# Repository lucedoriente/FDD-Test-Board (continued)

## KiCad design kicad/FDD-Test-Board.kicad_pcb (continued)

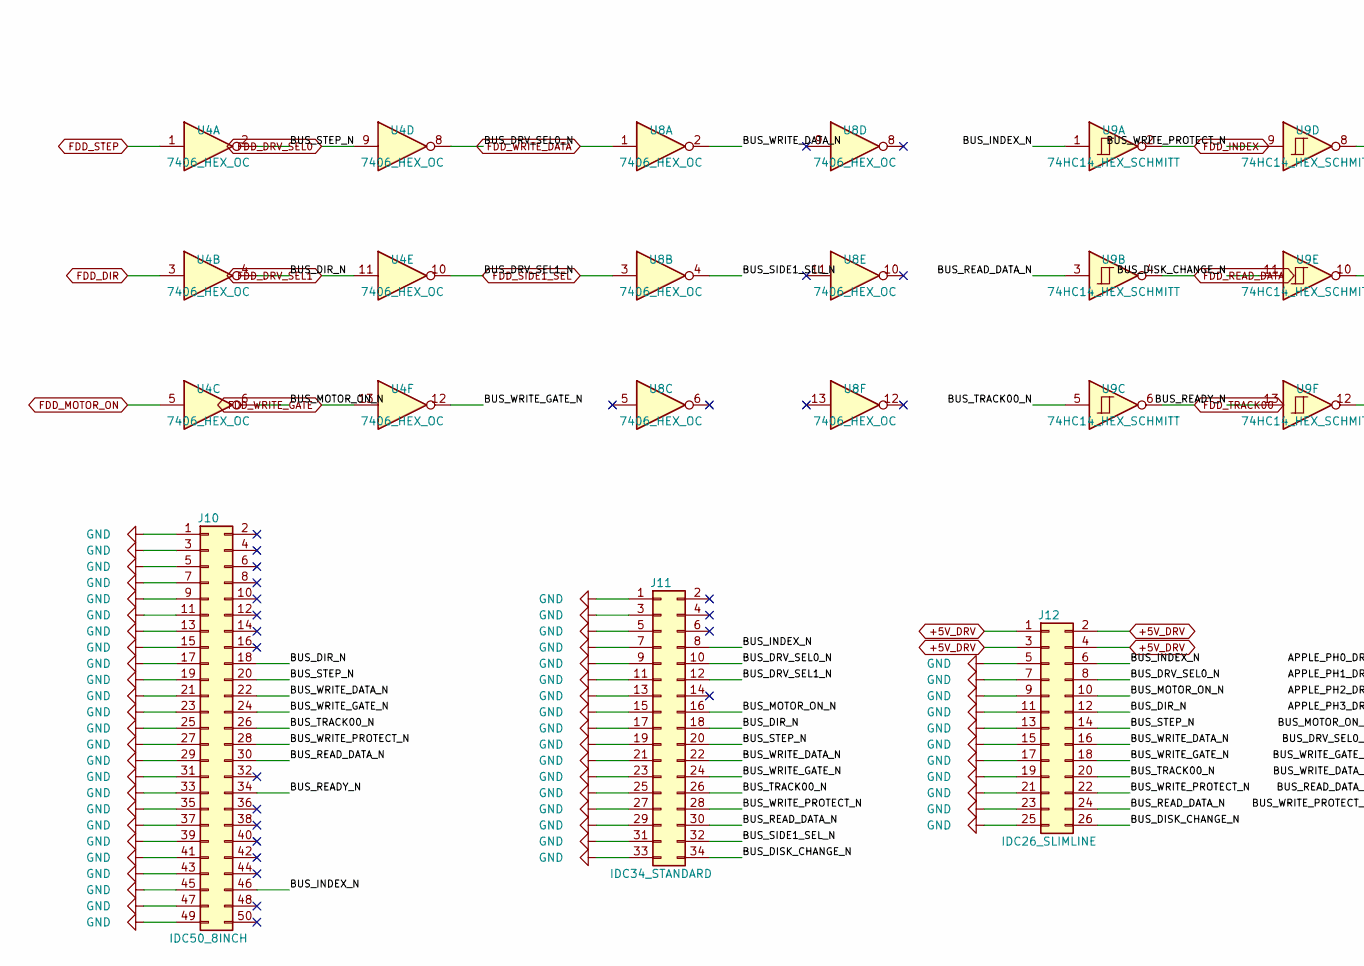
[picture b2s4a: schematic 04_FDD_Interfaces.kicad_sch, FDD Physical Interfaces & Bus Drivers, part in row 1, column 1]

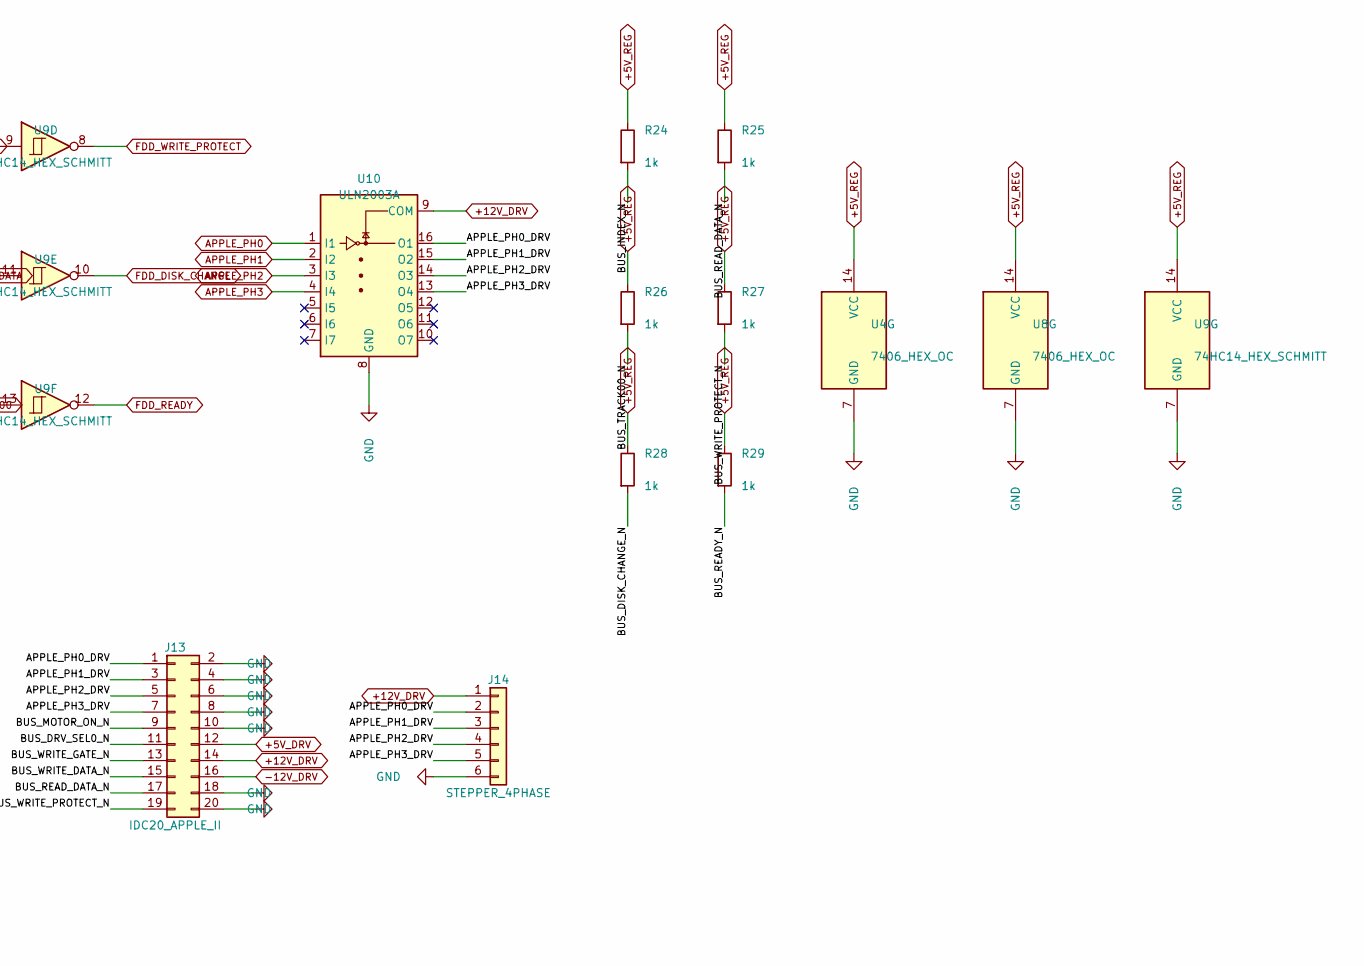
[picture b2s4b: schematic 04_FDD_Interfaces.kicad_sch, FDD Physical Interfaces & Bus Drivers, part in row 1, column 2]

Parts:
J10: IDC50_8INCH; IDC-Header_2x25_P2.54mm_Horizontal
J11: IDC34_STANDARD; IDC-Header_2x17_P2.54mm_Horizontal
J12: IDC26_SLIMLINE; IDC-Header_2x13_P2.54mm_Horizontal
J13: IDC20_APPLE_II; IDC-Header_2x10_P2.54mm_Horizontal
J14: STEPPER_4PHASE; PinHeader_1x06_P2.54mm_Horizontal
R24, R25, R26, R27, R28, R29: 1k; R_0805_2012Metric
U4, U8: 7406_HEX_OC; SOIC-14_3.9x8.7mm_P1.27mm
U9: 74HC14_HEX_SCHMITT; SOIC-14_3.9x8.7mm_P1.27mm
U10: ULN2003A; SOIC-16_3.9x9.9mm_P1.27mm

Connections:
+5V_DRV: J12.1, J12.2, J12.3, J12.4, J13.12; also elsewhere on the board
+5V_REG: R24.1, R25.1, R26.1, R27.1, R28.1, R29.1, U4.14 (VCC), U8.14 (VCC), U9.14 (VCC); also elsewhere on the board
+12V_DRV: J13.14, J14.1, U10.9 (COM); also elsewhere on the board
-12V_DRV: J13.16; also elsewhere on the board
/FDD_Interfaces/APPLE_PH0_DRV: J13.1, J14.2, U10.16 (O1)
/FDD_Interfaces/APPLE_PH1_DRV: J13.3, J14.3, U10.15 (O2)
/FDD_Interfaces/APPLE_PH2_DRV: J13.5, J14.4, U10.14 (O3)
/FDD_Interfaces/APPLE_PH3_DRV: J13.7, J14.5, U10.13 (O4)
/FDD_Interfaces/BUS_DIR_N: J10.18, J11.18, J12.12, U4.4
/FDD_Interfaces/BUS_DISK_CHANGE_N: J11.34, J12.26, R28.2, U9.11
/FDD_Interfaces/BUS_DRV_SEL0_N: J11.10, J12.8, J13.11, U4.8
/FDD_Interfaces/BUS_DRV_SEL1_N: J11.12, U4.10
/FDD_Interfaces/BUS_INDEX_N: J10.46, J11.8, J12.6, R24.2, U9.1
/FDD_Interfaces/BUS_MOTOR_ON_N: J11.16, J12.10, J13.9, U4.6
/FDD_Interfaces/BUS_READY_N: J10.34, R29.2, U9.13
/FDD_Interfaces/BUS_READ_DATA_N: J10.30, J11.30, J12.24, J13.17, R25.2, U9.3
/FDD_Interfaces/BUS_SIDE1_SEL_N: J11.32, U8.4
/FDD_Interfaces/BUS_STEP_N: J10.20, J11.20, J12.14, U4.2
/FDD_Interfaces/BUS_TRACK00_N: J10.26, J11.26, J12.20, R26.2, U9.5
/FDD_Interfaces/BUS_WRITE_DATA_N: J10.22, J11.22, J12.16, J13.15, U8.2
/FDD_Interfaces/BUS_WRITE_GATE_N: J10.24, J11.24, J12.18, J13.13, U4.12
/FDD_Interfaces/BUS_WRITE_PROTECT_N: J10.28, J11.28, J12.22, J13.19, R27.2, U9.9
APPLE_PH0: U10.1 (I1); also elsewhere on the board
APPLE_PH1: U10.2 (I2); also elsewhere on the board
APPLE_PH2: U10.3 (I3); also elsewhere on the board
APPLE_PH3: U10.4 (I4); also elsewhere on the board
FDD_DIR: U4.3; also elsewhere on the board
FDD_DISK_CHANGE: U9.10; also elsewhere on the board
FDD_DRV_SEL0: U4.9; also elsewhere on the board
FDD_DRV_SEL1: U4.11; also elsewhere on the board
FDD_INDEX: U9.2; also elsewhere on the board
FDD_MOTOR_ON: U4.5; also elsewhere on the board
FDD_READY: U9.12; also elsewhere on the board
FDD_READ_DATA: U9.4; also elsewhere on the board
FDD_SIDE1_SEL: U8.3; also elsewhere on the board
FDD_STEP: U4.1; also elsewhere on the board
FDD_TRACK00: U9.6; also elsewhere on the board
FDD_WRITE_DATA: U8.1; also elsewhere on the board
FDD_WRITE_GATE: U4.13; also elsewhere on the board
FDD_WRITE_PROTECT: U9.8; also elsewhere on the board
GND: J10.1, J10.3, J10.5, J10.7, J10.9, J10.11, J10.13, J10.15, J10.17, J10.19, J10.21, J10.23, J10.25, J10.27, J10.29, J10.31, J10.33, J10.35, J10.37, J10.39, J10.41, J10.43, J10.45, J10.47, J10.49, J11.1, J11.3, J11.5, J11.7, J11.9, J11.11, J11.13, J11.15, J11.17, J11.19, J11.21, J11.23, J11.25, J11.27, J11.29, J11.31, J11.33, J12.5, J12.7, J12.9, J12.11, J12.13, J12.15, J12.17, J12.19, J12.21, J12.23, J12.25, J13.2, J13.4, J13.6, J13.8, J13.10, J13.18, J13.20, J14.6, U4.7 (GND), U8.7 (GND), U9.7 (GND), U10.8 (GND); also elsewhere on the board

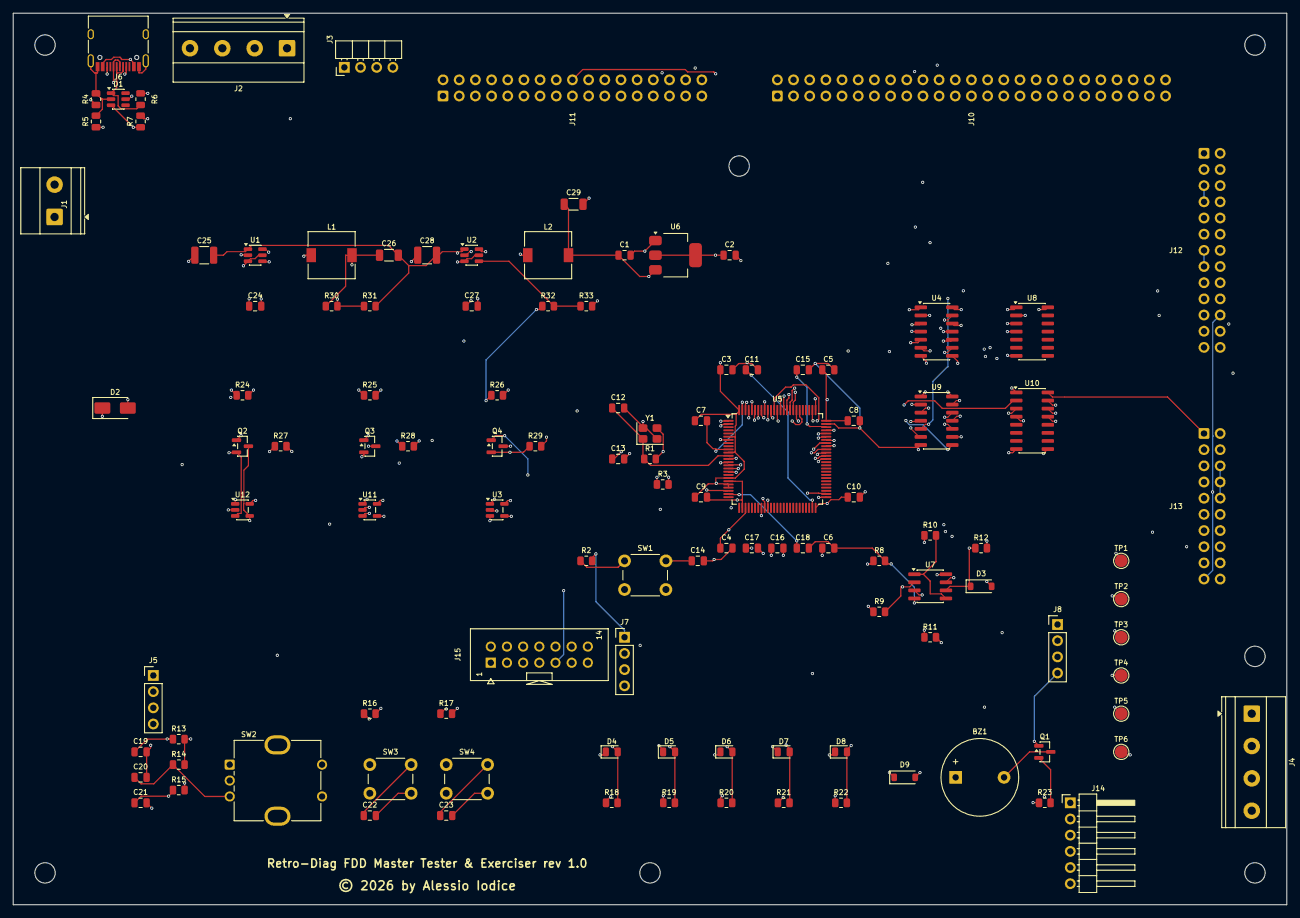
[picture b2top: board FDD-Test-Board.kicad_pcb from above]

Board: 4 copper layers, 200.0 x 140.0 mm, 122 parts (0 on the bottom side), 100 nets.

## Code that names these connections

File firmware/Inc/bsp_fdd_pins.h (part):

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/* ========================================================================== */

/* Power Rails Enable Pins (Active HIGH) */
#define EN_24V_PORT             GPIOC
#define EN_24V_PIN              GPIO_PIN_4         /* Pin 33 */

#define EN_12V_PORT             GPIOC
#define EN_12V_PIN              GPIO_PIN_5         /* Pin 34 */

#define EN_5V_PORT              GPIOB
#define EN_5V_PIN               GPIO_PIN_0         /* Pin 35 */

/* Analog Current Sensing (INA180A1 with Gain = 20 V/V, Shunt = 0.05 Ohm) */
#define ISENSE_24V_PORT         GPIOC
#define ISENSE_24V_PIN          GPIO_PIN_0         /* Pin 15, ADC1_IN10 */
#define ISENSE_24V_ADC_CH       ADC_CHANNEL_10

#define ISENSE_12V_PORT         GPIOC
#define ISENSE_12V_PIN          GPIO_PIN_1         /* Pin 16, ADC1_IN11 */
#define ISENSE_12V_ADC_CH       ADC_CHANNEL_11

#define ISENSE_5V_PORT          GPIOC
#define ISENSE_5V_PIN           GPIO_PIN_2         /* Pin 17, ADC1_IN12 */
#define ISENSE_5V_ADC_CH        ADC_CHANNEL_12

/* Shunt & Amplifier Parameters */
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 * At power-on, all pins MUST be set to LOW to keep the drive completely idle.
 */

#define FDD_READY_PORT          GPIOD
#define FDD_READY_PIN           GPIO_PIN_0         /* Pin 81 */

#define FDD_STEP_PORT           GPIOD
#define FDD_STEP_PIN            GPIO_PIN_1         /* Pin 82 */

#define FDD_DIR_PORT            GPIOD
#define FDD_DIR_PIN             GPIO_PIN_2         /* Pin 83: HIGH=In (Cylinder++), LOW=Out (Cylinder--) */

#define FDD_MOTOR_ON_PORT       GPIOD
#define FDD_MOTOR_ON_PIN        GPIO_PIN_3         /* Pin 84 */

#define FDD_DRV_SEL0_PORT       GPIOD
#define FDD_DRV_SEL0_PIN        GPIO_PIN_4         /* Pin 85 */

#define FDD_DRV_SEL1_PORT       GPIOD
#define FDD_DRV_SEL1_PIN        GPIO_PIN_5         /* Pin 86 */

#define FDD_SIDE1_SEL_PORT      GPIOD
#define FDD_SIDE1_SEL_PIN       GPIO_PIN_6         /* Pin 87: HIGH=Side 1, LOW=Side 0 */

#define FDD_WRITE_GATE_PORT     GPIOD
#define FDD_WRITE_GATE_PIN      GPIO_PIN_7         /* Pin 88 */

#define FDD_WRITE_DATA_PORT     GPIOB
#define FDD_WRITE_DATA_PIN      GPIO_PIN_9         /* Pin 96 */

/* ========================================================================== */
/* 3. FDD BUS SENSOR INPUTS (Conditioned via 74HC14 Schmitt Trigger Inverters) */
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 * Therefore, a HIGH reading on these STM32 inputs represents ACTIVE condition.
 */

#define FDD_TRACK00_PORT        GPIOB
#define FDD_TRACK00_PIN         GPIO_PIN_3         /* Pin 89: 1 = At Track 00 */

#define FDD_WRITE_PROTECT_PORT  GPIOB
#define FDD_WRITE_PROTECT_PIN   GPIO_PIN_4         /* Pin 90: 1 = Disk is Write Protected */

#define FDD_DISK_CHANGE_PORT    GPIOB
#define FDD_DISK_CHANGE_PIN     GPIO_PIN_5         /* Pin 91: 1 = Disk changed / Door opened */

#define FDD_INDEX_PORT          GPIOB
#define FDD_INDEX_PIN           GPIO_PIN_6         /* Pin 92: TIM4_CH1 Input Capture */

#define FDD_READ_DATA_PORT      GPIOB
#define FDD_READ_DATA_PIN       GPIO_PIN_7         /* Pin 93: TIM4_CH2 Input Capture */

/* ========================================================================== */
/* 4. DIRECT 4-PHASE UNIPOLAR STEPPER DRIVE (Apple II / C1541 via ULN2003A)    */
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 * - STM32 LOW (0V)   -> Darlington OFF       -> Coil unenergized.
 */
#define APPLE_STEPPER_PORT      GPIOE
#define APPLE_PH0_PIN           GPIO_PIN_0         /* Pin 97 */
#define APPLE_PH1_PIN           GPIO_PIN_1         /* Pin 98 */
#define APPLE_PH2_PIN           GPIO_PIN_2         /* Pin 1  */
#define APPLE_PH3_PIN           GPIO_PIN_3         /* Pin 2  */
#define APPLE_PH_ALL_MASK       (GPIO_PIN_0 | GPIO_PIN_1 | GPIO_PIN_2 | GPIO_PIN_3)

/* ========================================================================== */
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/* ========================================================================== */

/* Physical Pushbuttons (Active LOW, internal/external pull-ups) */
#define BTN_RUN_PORT            GPIOB
#define BTN_RUN_PIN             GPIO_PIN_12        /* Pin 51 */

#define BTN_BACK_PORT           GPIOB
#define BTN_BACK_PIN            GPIO_PIN_13        /* Pin 52 */

#define ENC_SW_PORT             GPIOC
#define ENC_SW_PIN              GPIO_PIN_13        /* Pin 7 */

#define ENC_A_PORT              GPIOA
#define ENC_A_PIN               GPIO_PIN_0         /* Pin 23, EXTI0 */

#define ENC_B_PORT              GPIOA
#define ENC_B_PIN               GPIO_PIN_15        /* Pin 77, EXTI15 */

/* Status Indicators (Active HIGH) */
#define LED_READY_PORT          GPIOC
#define LED_READY_PIN           GPIO_PIN_6         /* Pin 63 (Green) */

#define LED_BUSY_PORT           GPIOC
#define LED_BUSY_PIN            GPIO_PIN_7         /* Pin 64 (Yellow) */

#define LED_FAULT_PORT          GPIOC
#define LED_FAULT_PIN           GPIO_PIN_8         /* Pin 65 (Red) */

#define LED_INDEX_PORT          GPIOC
#define LED_INDEX_PIN           GPIO_PIN_9         /* Pin 66 (Blue) */

#define LED_READ_PORT           GPIOA
#define LED_READ_PIN            GPIO_PIN_8         /* Pin 67 (Orange) */

/* Audible Buzzer (TIM4_CH3 or GPIO) */
#define BUZZER_PORT             GPIOB
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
